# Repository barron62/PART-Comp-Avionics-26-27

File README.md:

# PART-Avionics-26-27
PART (Purdue Aerial Robotics Team) PCBs accompanying embedded code
Custom PCBS:
 PDU (power distribution unit)
 Pixhawk Carrier Board
 Battery Bleed Board
 Sensor Board
 Thrust Stand Board

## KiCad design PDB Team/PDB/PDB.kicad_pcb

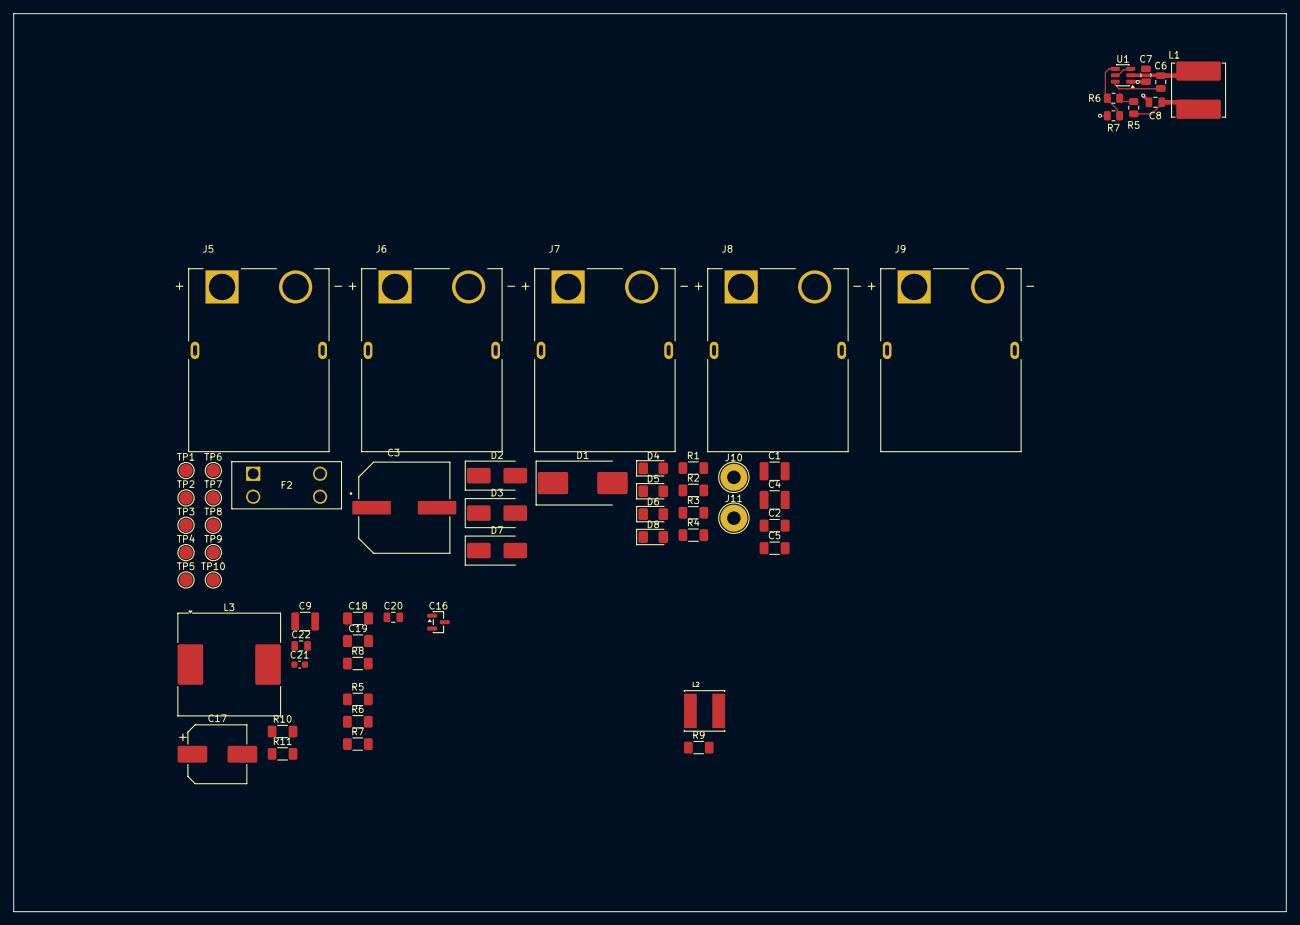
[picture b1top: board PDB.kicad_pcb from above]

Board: 2 copper layers, 188.5 x 133.0 mm, 60 parts (0 on the bottom side), 20 nets.

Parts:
C1, C4: 2.2 uF; C_1210_3225Metric_Pad1.33x2.70mm_HandSolder
C2, C5: 0.1 uF; C_1206_3216Metric_Pad1.33x1.80mm_HandSolder
C3: 100 uF; CAP_EEEFK1K101AQ
C6, C20, C22: 100nF; C_0805_2012Metric
C7, C8: 10uF; C_0805_2012Metric
C9: 10uF; C_1210_3225Metric
C16: 22uF; SOT-23
C17: 100uF; CP_Elec_8x10.5
C18, C19: 2.2uF; C_1206_3216Metric_Pad1.33x1.80mm_HandSolder
C21: 100nF; C_0603_1608Metric
D1: SMCJ51A; D_SMC_Handsoldering
D2: SMBJ26A; D_SMB_Handsoldering
D3: SMBJ5.0A; D_SMB_Handsoldering
D4, D5, D6, D8: APT3216SGC; LED_1206_3216Metric_Pad1.42x1.75mm_HandSolder
D7: SMBJ20A; D_SMB_Handsoldering
F2: 3568; 3568_KEY
J5, J6, J7, J8, J9: XT90PW-M; AMASS_XT90PW-M
J10: 12S+ Solder Hole; TestPoint_THTPad_D4.0mm_Drill2.0mm
J11: 12S- Solder Hole; TestPoint_THTPad_D4.0mm_Drill2.0mm
L1: 33uH; HPC8040NC-330M
L2: 47uH; IND_VLS6045EX-470M
L3: 33uH; L_Coilcraft_MSS1583-XXX
R1: 3.42k; R_1206_3216Metric_Pad1.30x1.75mm_HandSolder
R2: 560; R_1206_3216Metric_Pad1.30x1.75mm_HandSolder
R3: 220; R_1206_3216Metric_Pad1.30x1.75mm_HandSolder
R4: 3.16k; R_1206_3216Metric_Pad1.30x1.75mm_HandSolder
R5: 270k; R_0805_2012Metric
R5#2: 270k; R_1206_3216Metric_Pad1.30x1.75mm_HandSolder
R6: 180k; R_0805_2012Metric
R6#2, R8: 180k; R_1206_3216Metric_Pad1.30x1.75mm_HandSolder
R7: 100k; R_1206_3216Metric_Pad1.30x1.75mm_HandSolder
R7#2: 100k; R_0805_2012Metric
R9: 6.2k; R_1206_3216Metric_Pad1.30x1.75mm_HandSolder
R10: 215k; R_1206_3216Metric_Pad1.30x1.75mm_HandSolder
R11: 10k; R_1206_3216Metric_Pad1.30x1.75mm_HandSolder
TP1: 12S_V; TestPoint_Pad_D2.0mm
TP2: TP_24V; TestPoint_Pad_D2.0mm
TP3: TP_5V; TestPoint_Pad_D2.0mm
TP4: TP_3_3V; TestPoint_Pad_D2.0mm
TP5: TP_18V; TestPoint_Pad_D2.0mm
TP6, TP7, TP8, TP9, TP10: GND; TestPoint_Pad_D2.0mm
U1: TPP362080; TSOT-23-6

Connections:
+12S: C1.1, C2.1, C3.1, C4.1, C5.1, C9.1, C21.1, D1.1 (K), F2.3, F2.4, J5.P (POS), J6.P (POS), J7.P (POS), J8.P (POS), J9.P (POS), TP1.1 (1_1)
/5V_3_3V_LDO/3_3V: C16.1, R3.1, TP4.1 (1_1)
/5V_3_3V_LDO/5V: D3.1 (K), R2.1, TP3.1 (1_1)
/12S_18V_Buck/18V: C17.1, D7.1 (K), L3.2, R4.1, R10.1, TP5.1 (1_1)
/12S_24V_Buck/24V: C7.1, D2.1 (K), L2.2, R1.1, R8.1, TP2.1 (1_1), U1.3 (VIN), U1.5 (EN)
/24V_5V_Buck/5V: C8.1, L1.2, R5.1, R5#2.1
/VBAT+: F2.1, F2.2, J10.1 (1_1)
GND: C1.2, C2.2, C3.2, C4.2, C5.2, C7.2, C8.2, C9.2, C16.2, C17.2, C21.2, D1.2 (A), D2.2 (A), D3.2 (A), D4.1 (K), D5.1 (K), D6.1 (K), D7.2 (A), D8.1 (K), J5.N (NEG), J6.N (NEG), J7.N (NEG), J8.N (NEG), J9.N (NEG), J11.1 (1_1), R7.2, R7#2.2, R9.2, R11.2, TP6.1 (1_1), TP7.1 (1_1), TP8.1 (1_1), TP9.1 (1_1), TP10.1 (1_1), U1.1 (GND)
unnamed: D4.2 (A), R1.2
unnamed: D5.2 (A), R2.2
unnamed: D6.2 (A), R3.2
unnamed: D8.2 (A), R4.2
unnamed: R5.2, R5#2.2, R6.1, R6#2.1
unnamed: C6.2, L1.1, U1.2 (SW)
unnamed: C6.1, U1.6 (VBST)
unnamed: R6.2, R6#2.2, R7.1, R7#2.1, U1.4 (VFB)
unnamed: R8.2, R9.1
unnamed: C20.2, L2.1
unnamed: R10.2, R11.1
unnamed: C22.2, L3.1

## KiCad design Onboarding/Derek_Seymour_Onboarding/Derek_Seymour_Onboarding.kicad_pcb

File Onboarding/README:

Comp Avionics Onboarding Project

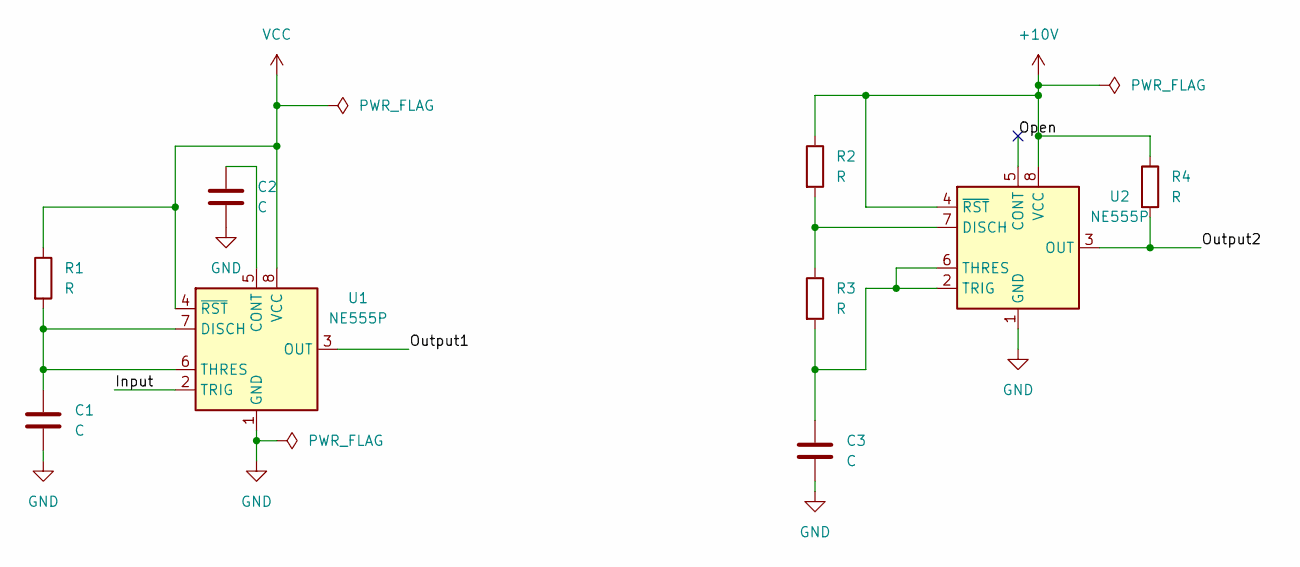
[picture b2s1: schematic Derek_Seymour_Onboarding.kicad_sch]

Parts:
C1, C2, C3: C; C_Elec_4x5.4
R1, R2: R; DIP-8_W7.62mm
R3, R4: R; R_0805_2012Metric
U1, U2: NE555P; DIP-8_W7.62mm

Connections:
+10V: R2.1, R4.1, U2.4 (~RST), U2.8 (VCC)
/Input: U1.2 (TRIG)
/Open: U2.5 (CONT)
/Output: U1.3 (OUT)
/Output2: R4.2, U2.3 (OUT)
GND: C1.2, C2.2, C3.2, U1.1 (GND), U2.1 (GND)
unnamed: C2.1, U1.5 (CONT)
unnamed: C1.1, R1.2, U1.6 (THRES), U1.7 (DISCH)
unnamed: R2.2, R3.1, U2.7 (DISCH)
unnamed: C3.1, R3.2, U2.2 (TRIG), U2.6 (THRES)
VCC: R1.1, U1.4 (~RST), U1.8 (VCC)

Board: 2 copper layers, 9 parts (0 on the bottom side), 8 nets, no tracks yet.

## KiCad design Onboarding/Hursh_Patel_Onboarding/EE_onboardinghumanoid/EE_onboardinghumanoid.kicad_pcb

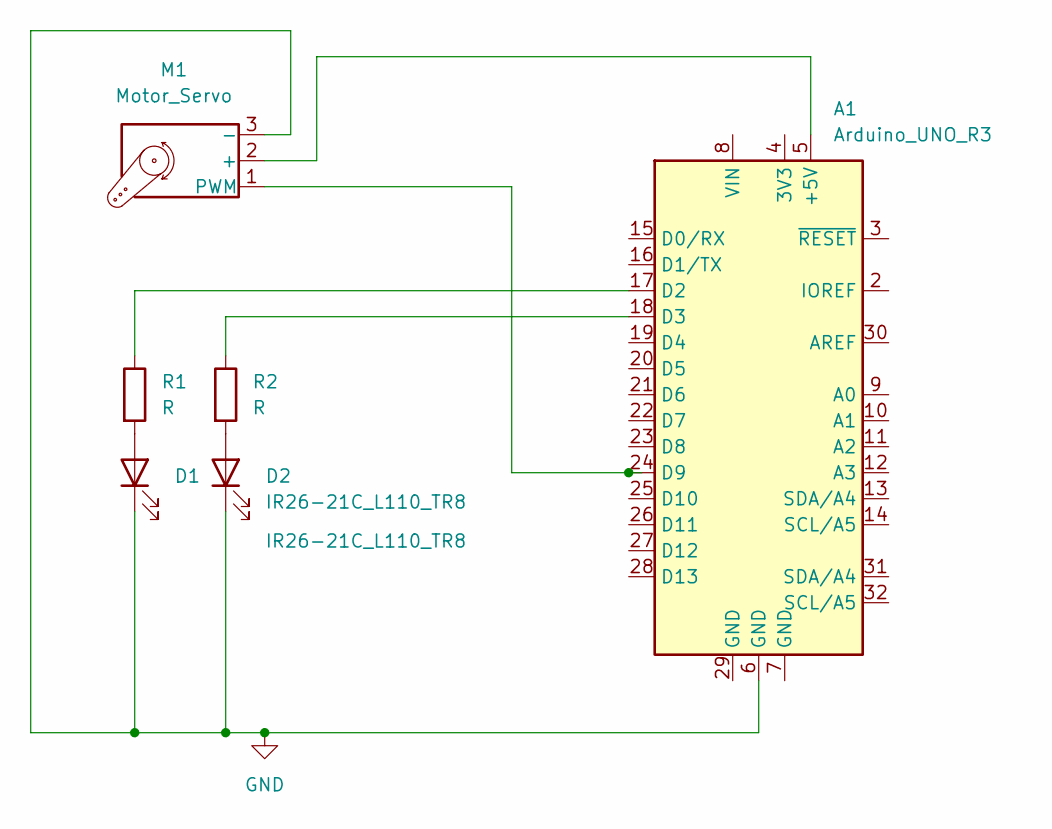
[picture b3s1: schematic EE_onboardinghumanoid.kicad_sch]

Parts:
A1: Arduino_UNO_R3
D1, D2: IR26-21C_L110_TR8; LED_D3.0mm
M1: Motor_Servo; PinHeader_1x30_P1.00mm_Horizontal
R1, R2: R; R_Axial_DIN0207_L6.3mm_D2.5mm_P7.62mm_Horizontal

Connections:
GND: A1.6 (GND), D1.1 (K), D2.1 (K), M1.3 (-)
unnamed: A1.5 (+5V), M1.2 (+)
unnamed: A1.17 (D2), R1.1
unnamed: A1.18 (D3), R2.1
unnamed: A1.24 (D9), M1.1 (PWM)
unnamed: D1.2 (A), R1.2
unnamed: D2.2 (A), R2.2

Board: 2 copper layers, 6 parts (0 on the bottom side), 7 nets, no tracks yet.

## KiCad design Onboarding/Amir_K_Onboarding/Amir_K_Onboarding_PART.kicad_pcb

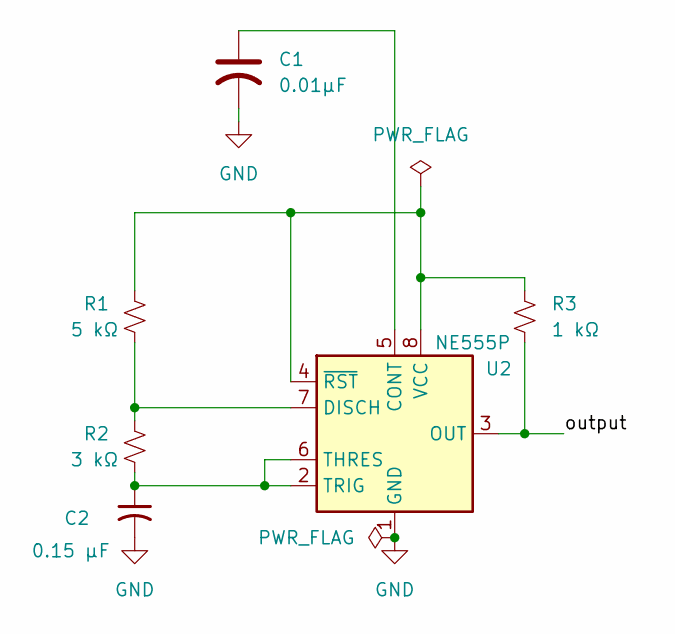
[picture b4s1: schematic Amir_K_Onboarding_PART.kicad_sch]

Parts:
C1: 0.01µF; C_1206_3216Metric
C2: 0.15 µF; C_1206_3216Metric
R1: 5 kΩ; R_1206_3216Metric
R2: 3 kΩ; R_1206_3216Metric
R3: 1 kΩ; R_1206_3216Metric
U2: NE555P; DIP-8_W7.62mm

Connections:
/output: R3.2, U2.3 (OUT)
GND: C1.2, C2.2, U2.1 (GND)
unnamed: C1.1, U2.5 (CONT)
unnamed: R1.2, R2.1, U2.7 (DISCH)
unnamed: C2.1, R2.2, U2.2 (TRIG), U2.6 (THRES)
unnamed: R1.1, R3.1, U2.4 (~RST), U2.8 (VCC)

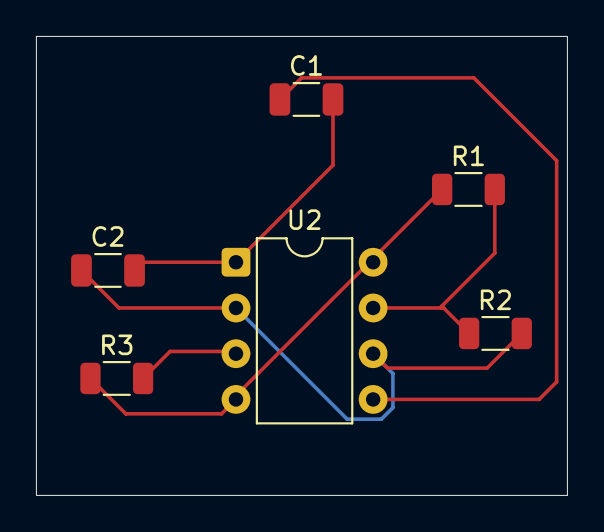
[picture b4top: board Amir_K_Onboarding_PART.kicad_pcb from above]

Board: 2 copper layers, 29.5 x 25.5 mm, 6 parts (0 on the bottom side), 6 nets.

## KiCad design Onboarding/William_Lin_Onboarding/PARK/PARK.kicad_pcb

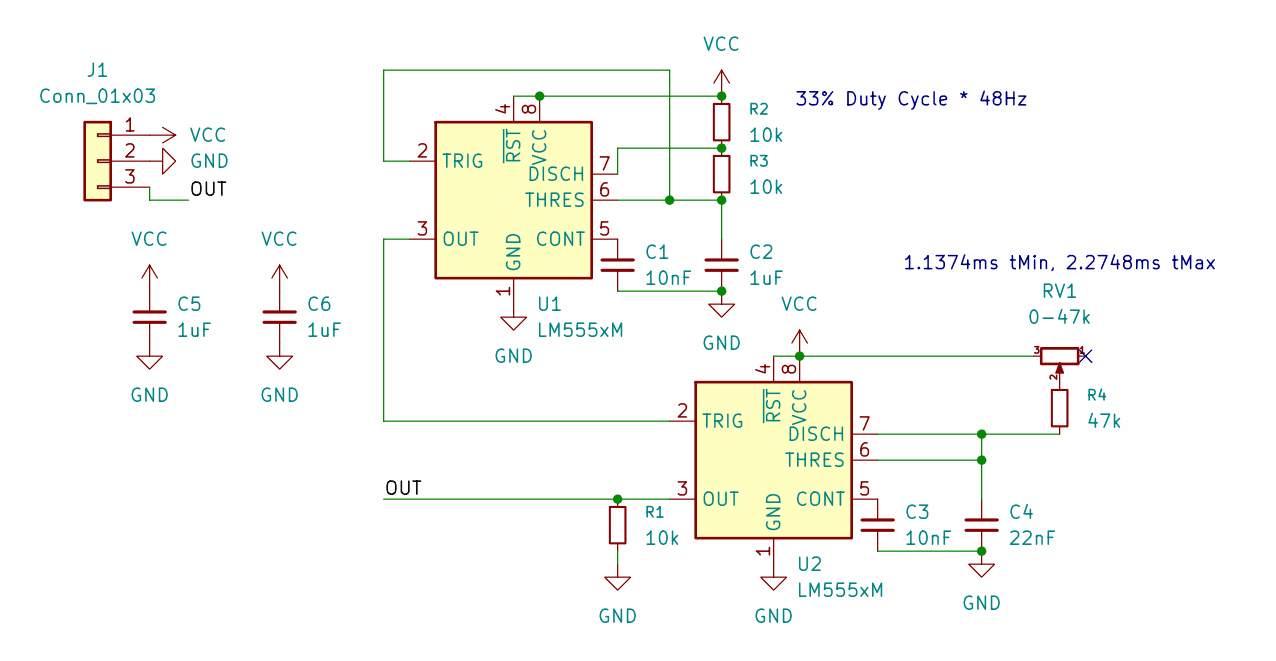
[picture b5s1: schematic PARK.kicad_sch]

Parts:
C1, C3: 10nF; C_0805_2012Metric_Pad1.18x1.45mm_HandSolder
C2, C5, C6: 1uF; C_0805_2012Metric_Pad1.18x1.45mm_HandSolder
C4: 22nF; C_0805_2012Metric_Pad1.18x1.45mm_HandSolder
J1: Conn_01x03; JST_XH_B3B-XH-AM_1x03_P2.50mm_Vertical
R1, R2, R3: 10k; R_0805_2012Metric_Pad1.20x1.40mm_HandSolder
R4: 47k; R_0805_2012Metric_Pad1.20x1.40mm_HandSolder
RV1: 0-47k; Potentiometer_Bourns_PTV09A-1_Single_Vertical
U1, U2: LM555xM; SOIC-8_3.9x4.9mm_P1.27mm

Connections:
/OUT: J1.3, R1.1, U2.3 (OUT)
GND: C1.2, C2.2, C3.2, C4.2, C5.2, C6.2, J1.2, R1.2, U1.1 (GND), U2.1 (GND)
unnamed: R4.1, RV1.2
unnamed: C1.1, U1.5 (CONT)
unnamed: R2.2, R3.1, U1.7 (DISCH)
unnamed: U1.3 (OUT), U2.2 (TRIG)
unnamed: C2.1, R3.2, U1.2 (TRIG), U1.6 (THRES)
unnamed: C3.1, U2.5 (CONT)
unnamed: C4.1, R4.2, U2.6 (THRES), U2.7 (DISCH)
VCC: C5.1, C6.1, J1.1, R2.1, RV1.3, U1.4 (~RST), U1.8 (VCC), U2.4 (~RST), U2.8 (VCC)

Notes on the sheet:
1.1374ms tMin, 2.2748ms tMax
33% Duty Cycle * 48Hz

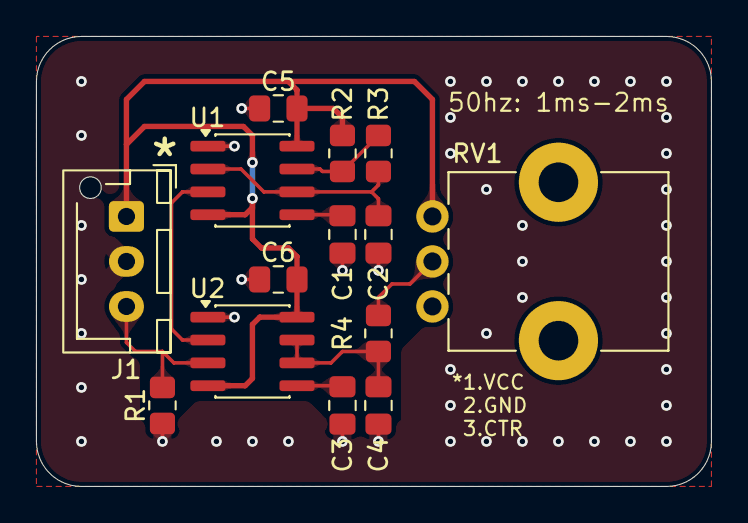
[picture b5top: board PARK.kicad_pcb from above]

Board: 2 copper layers, 37.5 x 25.0 mm, 14 parts (0 on the bottom side), 10 nets.

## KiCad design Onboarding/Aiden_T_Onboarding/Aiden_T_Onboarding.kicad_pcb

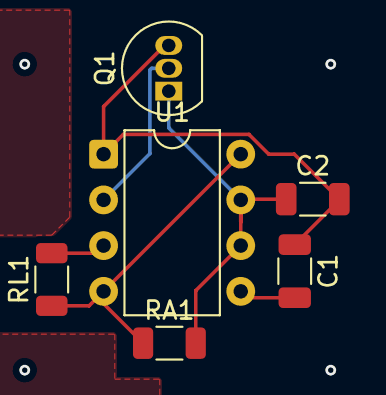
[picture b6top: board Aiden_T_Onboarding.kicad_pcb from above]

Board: 2 copper layers, 10 parts (0 on the bottom side), 6 nets.

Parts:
C1: 0.01μF; C_1206_3216Metric
C2: C; C_1206_3216Metric
H1, H2, H3, H4: MountingHole; MountingHole_4.3mm_M4
Q1: BC338; TO-92_Inline
RA1: R; R_1206_3216Metric
RL1: R; R_1206_3216Metric
U1: NE555P; DIP-8_W7.62mm

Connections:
GND: C1.1, C2.2, Q1.3 (E), U1.1 (GND)
IN: Q1.2 (B), U1.2 (TRIG)
unnamed: C2.1, Q1.1 (C), RA1.2, U1.6 (THRES), U1.7 (DISCH)
unnamed: C1.2, U1.5 (CONT)
OUT: RL1.2, U1.3 (OUT)
VCC: RA1.1, RL1.1, U1.4 (~RST), U1.8 (VCC)

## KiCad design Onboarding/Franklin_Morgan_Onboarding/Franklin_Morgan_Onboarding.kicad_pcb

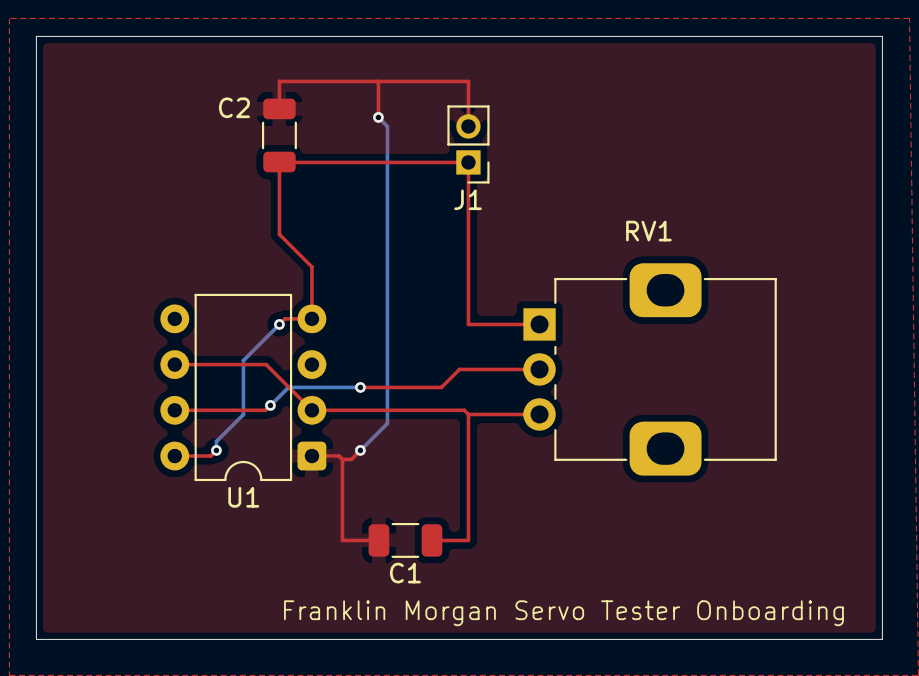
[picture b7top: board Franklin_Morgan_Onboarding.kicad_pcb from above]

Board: 2 copper layers, 47.0 x 33.5 mm, 5 parts (0 on the bottom side), 4 nets.

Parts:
C1: 0.15pF; C_1206_3216Metric
C2: 0.01uF; C_1206_3216Metric
J1: Conn_01x02_Pin; PinHeader_1x02_P2.00mm_Vertical
RV1: 1-10k; Potentiometer_Alps_RK09K_Single_Vertical
U1: NE555P; DIP-8_W7.62mm

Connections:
+5V: C2.1, J1.1, RV1.1, U1.4 (~RST), U1.8 (VCC)
GND: C1.2, C2.2, J1.2, U1.1 (GND)
unnamed: RV1.2, U1.7 (DISCH)
unnamed: C1.1, RV1.3, U1.2 (TRIG), U1.6 (THRES)

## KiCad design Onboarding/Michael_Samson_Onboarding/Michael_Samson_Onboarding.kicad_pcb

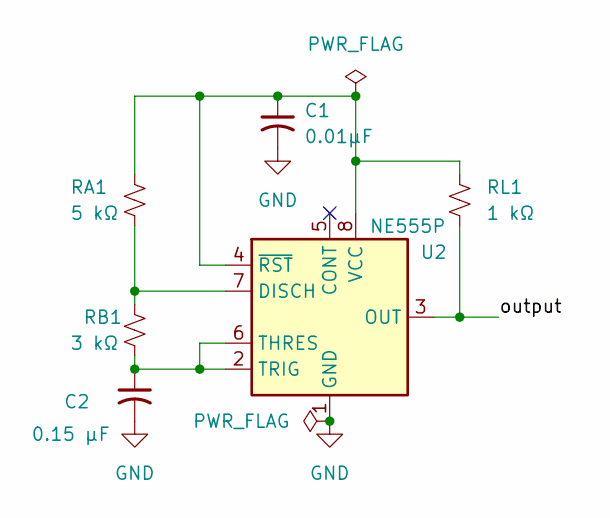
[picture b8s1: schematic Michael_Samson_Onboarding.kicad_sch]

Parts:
C1: 0.01µF; C_1206_3216Metric
C2: 0.15 µF; C_1206_3216Metric
RA1: 5 kΩ; R_1206_3216Metric
RB1: 3 kΩ; R_1206_3216Metric
RL1: 1 kΩ; R_1206_3216Metric
U2: NE555P; DIP-8_W7.62mm

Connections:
/output: RL1.2, U2.3 (OUT)
GND: C1.2, C2.2, U2.1 (GND)
unnamed: RA1.2, RB1.1, U2.7 (DISCH)
unnamed: C2.1, RB1.2, U2.2 (TRIG), U2.6 (THRES)
unnamed: C1.1, RA1.1, RL1.1, U2.4 (~RST), U2.8 (VCC)

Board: 2 copper layers, 6 parts (0 on the bottom side), 5 nets, no tracks yet.
